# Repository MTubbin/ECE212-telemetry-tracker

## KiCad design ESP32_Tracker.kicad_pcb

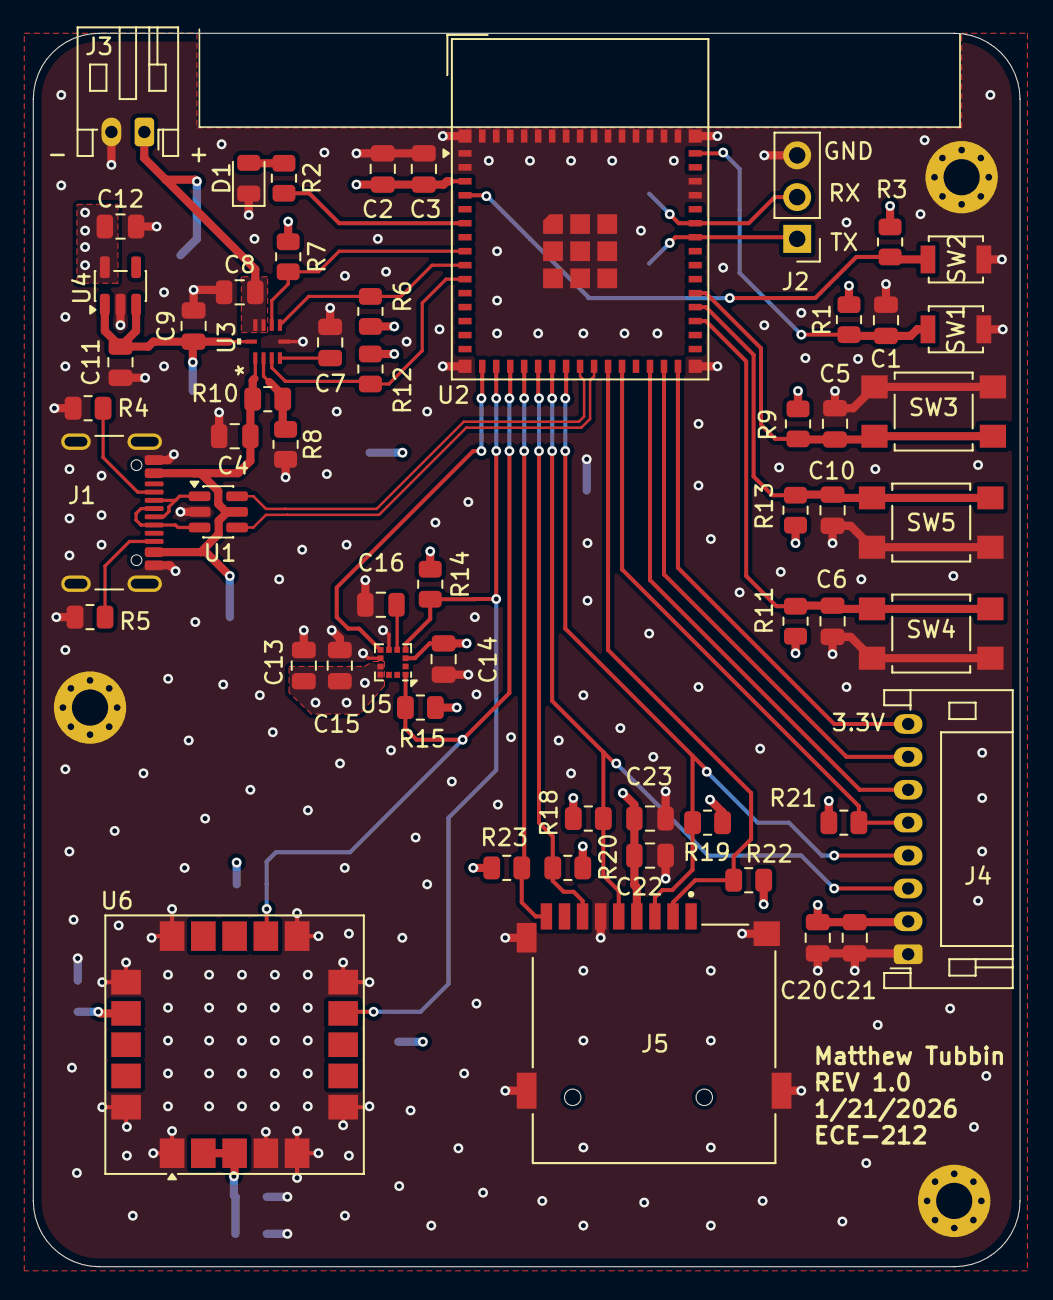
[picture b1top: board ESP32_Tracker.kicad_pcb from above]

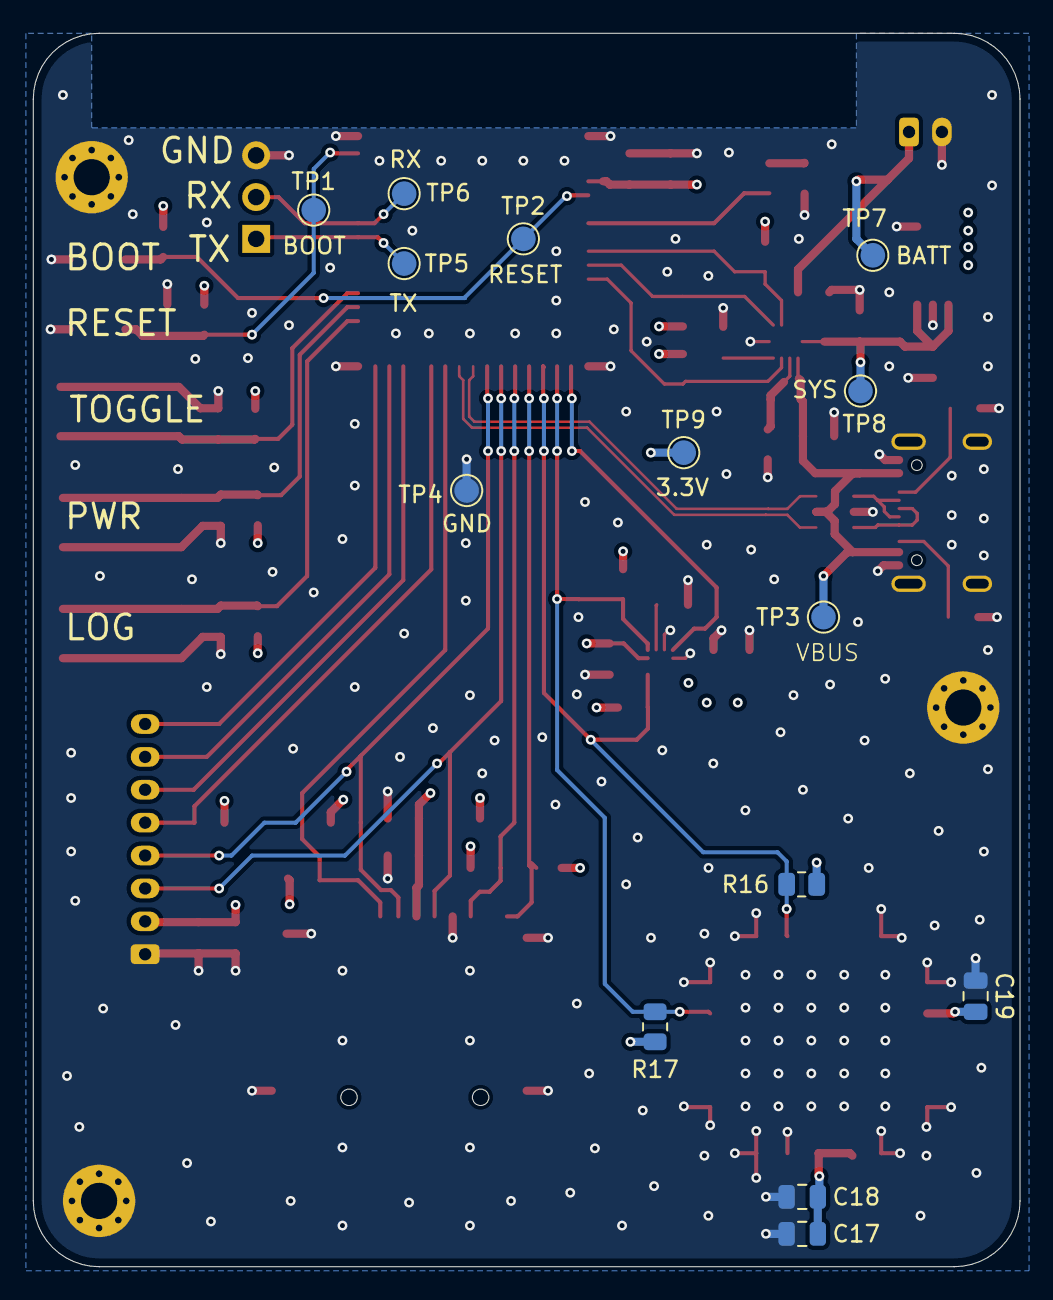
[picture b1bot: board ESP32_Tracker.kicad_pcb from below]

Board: 4 copper layers, 60.0 x 75.0 mm, 75 parts (14 on the bottom side), 38 nets.

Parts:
C1, C4: 1u; C_0805_2012Metric
C2: 22u; C_0805_2012Metric
C3, C5, C6, C7, C10, C14, C15, C18, C19, C21, C22: 0.1u; C_0805_2012Metric
C8, C11, C12, C13, C17, C20, C23: 10u; C_0805_2012Metric
C9: 2.2u; C_0805_2012Metric
C16: 0.22u; C_0805_2012Metric
D1: LED; LED_0805_2012Metric
H1, H2, H3: MountingHole_Pad; MountingHole_2.2mm_M2_Pad_Via
J1: USB_C_Receptacle_USB2.0_16P; USB_C_Receptacle_GCT_USB4105-xx-A_16P_TopMnt_Horizontal
J2: Conn_01x03; PinHeader_1x03_P2.54mm_Vertical
J3: Conn_01x02_Socket; JST_PH_S2B-PH-K_1x02_P2.00mm_Horizontal
J4: Conn_01x08_Socket; JST_PH_S8B-PH-K_1x08_P2.00mm_Horizontal
J5: MSD-4-A; CUI_MSD-4-A
R1, R3, R6, R7, R8, R9, R10, R11, R13, R14, R15, R18, R19, R20, R21, R22, R23: 10k; R_0805_2012Metric
R2, R16, R17: 2.2k; R_0805_2012Metric
R4, R5: 5.1k; R_0805_2012Metric
R12: 100k; R_0805_2012Metric
SW1, SW2: SW_Push; SW_SPST_B3U-1000P
SW3, SW4, SW5: SW_Push; SW_SPST_TL3305C
TP1, TP2, TP3, TP4, TP5, TP6, TP7, TP8, TP9: TestPoint; TestPoint_Pad_D1.5mm
U1: USBLC6-2SC6; SOT-23-6
U2: ESP32-S3-MINI-1; ESP32-S2-MINI-1
U3: MP2667; QFN-10_2MMx2MM_MNP
U4: XC6220B331MR-G; SOT-23-5
U5: LIS2MDL; LGA-12_2x2mm_P0.5mm
U6: SAM-M10Q; ublox_SAM-M8Q

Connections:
+3.3V: C2.1, C3.1, C12.1, C13.1, C14.1, C15.1, C17.1, C18.1, C19.1, C20.2, C21.1, C22.1, C23.1, J4.2, J5.4 (VDD), R1.2, R3.2, R6.2, R7.1, R9.2, R11.2, R12.1, R13.2, R14.2, R15.2, R16.2, R17.2, R18.1, R19.1, R20.1, R21.2, R22.1, R23.1, TP9.1, U2.3 (3V3), U4.5 (VOUT), U5.3 (~CS), U5.9 (Vdd), U5.10 (Vdd_IO), U6.2 (VCC_IO), U6.3 (V_BCKP), U6.17 (VCC)
+BATT: C8.2, J3.1, TP7.1, U3.8 (BATT), U3.9 (BATT)
/MCU/PWR/BATT_CLK: R6.1, U2.9 (IO5), U3.6 (SCL)
/MCU/PWR/BATT_DATA: R7.2, U2.8 (IO4), U3.7 (SDA)
/MCU/PWR/BATT_INT: R12.2, U2.10 (IO6), U3.3 (INT)
/MCU/PWR/GPS/MAG_CLK: R15.1, R16.1, U2.18 (IO14), U5.1 (SCL/SPC), U6.12 (SCL)
/MCU/PWR/GPS/MAG_DATA: R14.1, R17.1, U2.17 (IO13), U5.4 (SDA/SDI/SDO), U6.9 (SDA)
/MCU/PWR/MAG_INT: U2.16 (IO12), U5.7 (DRDY)
/MCU/PWR/OLED_CS: J4.5, R21.1, U2.26 (IO26)
/MCU/PWR/OLED_DC: J4.6, U2.28 (IO33)
/MCU/PWR/OLED_DET: J4.8, U2.30 (IO48)
/MCU/PWR/OLED_RST: J4.7, U2.29 (IO34)
/MCU/PWR/OLED/SD_MOSI: J4.4, J5.3 (CMD), R19.2, U2.22 (IO18)
/MCU/PWR/OLED/SD_SCK: J4.3, J5.5 (CLK), R18.2, U2.21 (IO17)
/MCU/PWR/RX: J2.2, TP6.1, U2.40 (RXD0)
/MCU/PWR/SD_CS: J5.2 (CD/DAT3), R22.2, U2.25 (IO21)
/MCU/PWR/SD_DETECT: J5.CD, R23.2, U2.19 (IO15)
/MCU/PWR/SD_MISO: J5.7 (DAT0), R20.2, U2.20 (IO16)
/MCU/PWR/SW_LOG: C6.1, R11.1, SW4.1, U2.33 (IO37)
/MCU/PWR/SW_PWR: C10.1, R13.1, SW5.1, U2.34 (IO38)
/MCU/PWR/SW_TOGGLE: C5.1, R9.1, SW3.2, U2.35 (IO39)
/MCU/PWR/TX: J2.1, TP5.1, U2.39 (TXD0)
/MCU/PWR/USB_D+: U1.4 (I/O2), U2.24 (USB_D+)
/MCU/PWR/USB_D-: U1.6 (I/O1), U2.23 (USB_D-)
GND: C1.2, C2.2, C3.2, C4.1, C5.2, C6.2, C7.2, C8.1, C9.2, C10.2, C11.1, C12.2, C13.2, C14.2, C15.2, C16.2, C17.2, C18.2, C19.2, C20.1, C21.2, C22.2, C23.2, D1.1 (K), H1.1, H2.1, H3.1, J1.A1 (GND), J1.A12 (GND), J1.B1 (GND), J1.B12 (GND), J1.S1 (SHIELD), J2.3, J3.2, J4.1, J5.6 (VSS), J5.G1 (COVER_GND), J5.G2 (COVER_GND__1), J5.G3 (COVER_GND__2), J5.G4 (COVER_GND__3), R4.1, R5.2, R8.2, SW1.1, SW2.2, SW3.1, SW4.2, SW5.2, TP4.1, U1.2 (GND), U2.1 (GND), U2.2 (GND), U2.42 (GND), U2.43 (GND), U2.46 (GND), U2.47 (GND), U2.48 (GND), U2.49 (GND), U2.50 (GND), U2.51 (GND), U2.52 (GND), U2.53 (GND), U2.54 (GND), U2.55 (GND), U2.56 (GND), U2.57 (GND), U2.58 (GND), U2.59 (GND), U2.60 (GND), U2.61 (GND), U2.62 (GND), U2.63 (GND), U2.64 (GND), U2.65 (GND), U3.5 (GND), U4.2 (GND), U5.6 (GND), U5.8 (GND), U6.1 (GND), U6.4 (GND), U6.5 (GND), U6.6 (GND), U6.10 (GND), U6.11 (GND), U6.15 (GND), U6.16 (GND), U6.20 (GND)
unnamed: D1.2 (A), R2.2
unnamed: J1.A5 (CC1), R4.2
unnamed: J1.B5 (CC2), R5.1
unnamed: J1.A6 (D+), J1.B6 (D+), U1.3 (I/O2)
unnamed: J1.A7 (D-), J1.B7 (D-), U1.1 (I/O1)
unnamed: C1.1, R1.1, SW1.2, TP1.1, U2.45 (EN)
unnamed: R3.1, SW2.1, TP2.1, U2.4 (IO0)
unnamed: R2.1, U2.6 (IO2)
unnamed: R8.1, R10.1, U3.2 (NTC)
unnamed: C9.1, C11.2, TP8.1, U3.10 (SYS), U4.1 (VIN), U4.3 (CE)
unnamed: C7.1, U3.4 (VDD)
unnamed: C16.1, U5.5 (C1)
VBUS: C4.2, J1.A4 (VBUS), J1.A9 (VBUS), J1.B4 (VBUS), J1.B9 (VBUS), R10.2, TP3.1, U1.5 (VBUS), U3.1 (IN)

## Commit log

2026-01-07 kicad files added
2026-01-08 initial schematic started
2026-01-08 magnt. symbol created
2026-01-09 new magnetometer
2026-01-11 initial schematic completed
2026-01-11 MP Footprint created
2026-01-11 models added
2026-01-13 notes
2026-01-13 initial board layout completed
2026-01-14 Layout completed
2026-01-14 modified layout
2026-01-15 modified and labeled layout
2026-01-16 added USBC programming
2026-01-16 modified BOM
2026-01-16 cleared DRC
2026-01-16 new push button
2026-01-17 modified battery terminal
2026-01-20 revised schematic
2026-01-21 changed to 8 pin connector
2026-01-22 REV 1.0 Ordered
2026-02-14 organized files
